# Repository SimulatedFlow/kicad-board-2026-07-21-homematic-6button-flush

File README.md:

# 2026-07-21-homematic-6button-flush

<!-- SF-STORE-BLOCK:BEGIN -->
## 🛒 Source-available — see before you buy

This repository contains the **full design files** of a commercial hardware board. It is **source-available, not open source**: read it, evaluate it, then buy a license to use it. See **LICENSE.md (source-available, purchase required)**.

**Get it / Buy:**
- **Order on eBay** (this board, bare PCB): https://www.ebay.de/itm/398220349166
- Product page (specs, photos, price): https://simulatedflow.teufel-engineering.com/platinen/2026-07-21-homematic-6button-flush/
- eBay store — all our boards and PCB art: https://www.ebay.de/usr/simula-9
- Merch shop (dev & gaming): https://simulatedflow.myspreadshop.de
- Merch shop (Synthetica / EDM): https://synthetica.myspreadshop.de
- Direct / invoice (Simulated Flow UG): simulatedflow@gmail.com

### 📬 **Free Board Documentation & Firmware Pack**

Schematics, BOMs and example-firmware docs for our STM32 carrier boards. Get it by joining the newsletter — plus a heads-up when something new ships. Double opt-in, unsubscribe in one click, no address sharing.

👉 **[Get the free pack](https://simulatedflow.teufel-engineering.com/newsletter/hardware/?q=gh)**

_© 2026 Simulated Flow UG. All rights reserved._
<!-- SF-STORE-BLOCK:END -->

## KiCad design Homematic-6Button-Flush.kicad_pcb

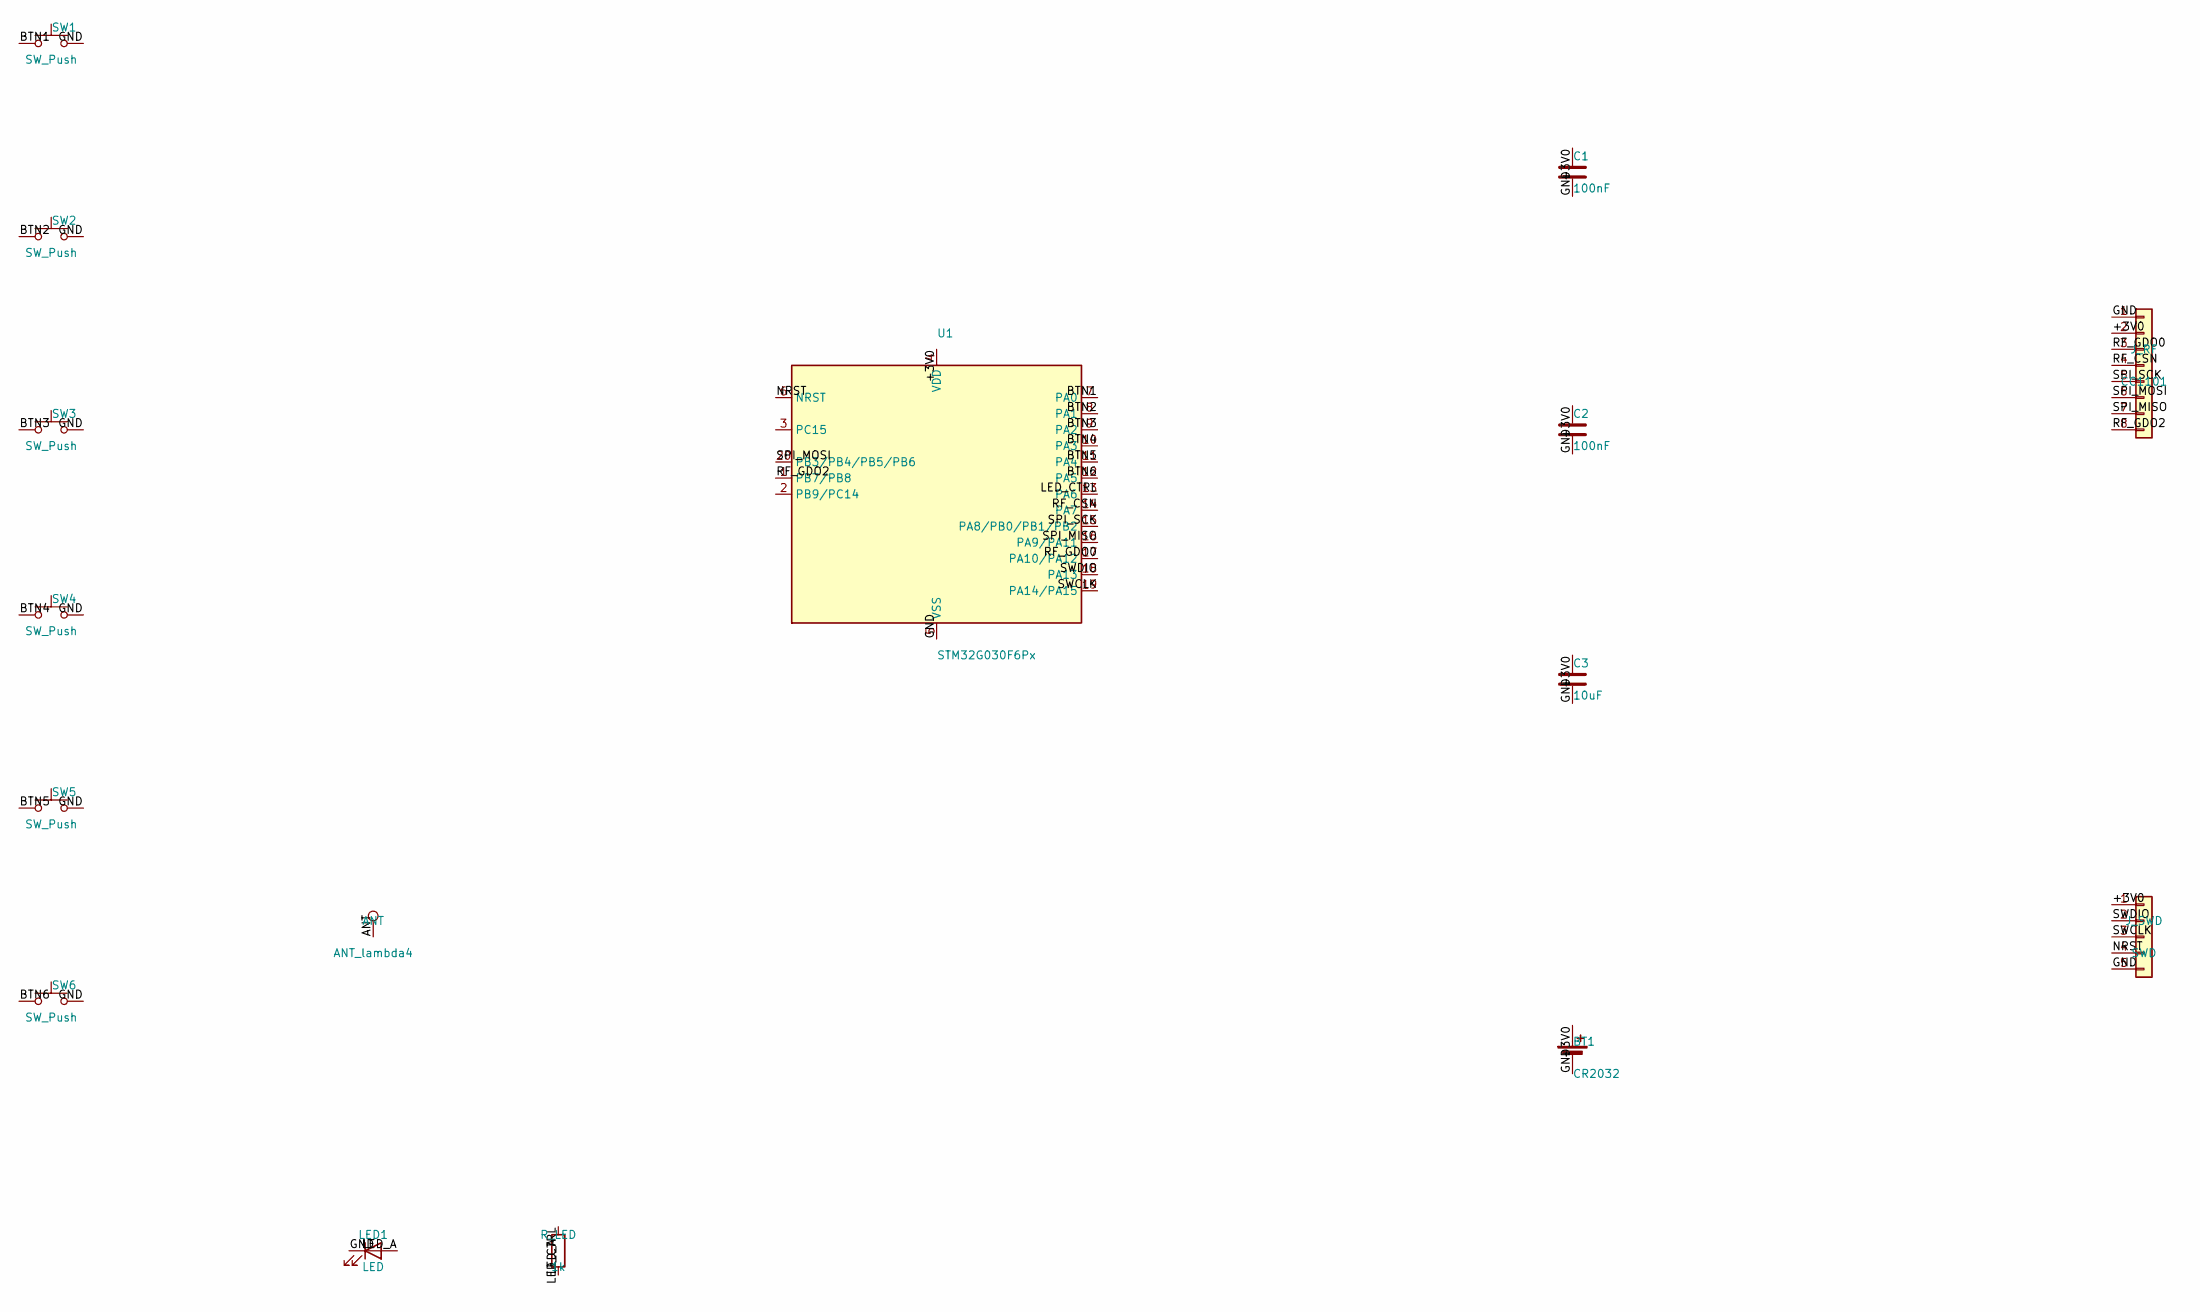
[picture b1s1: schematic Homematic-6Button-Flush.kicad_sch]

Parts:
ANT: ANT_lambda4; TestPoint_Pad_D2.0mm
BT1: CR2032; BatteryHolder_Keystone_3002_1x2032
C1, C2: 100nF; C_0603_1608Metric
C3: 10uF; C_0805_2012Metric
J_RF: CC1101; PinHeader_1x08_P2.54mm_Vertical
J_SWD: SWD; PinHeader_1x05_P2.54mm_Vertical
LED1: LED; LED_0805_2012Metric
R_LED: 1k; R_0603_1608Metric
SW1, SW2, SW3, SW4, SW5, SW6: SW_Push; SW_SPST_B3U-1000P
U1: STM32G030F6Px; TSSOP-20_4.4x6.5mm_P0.65mm

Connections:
+3V0: BT1.1 (+), C1.1, C2.1, C3.1, J_RF.2, J_SWD.1, U1.4 (VDD)
ANT: ANT.1
BTN1: SW1.1, U1.7 (PA0)
BTN2: SW2.1, U1.8 (PA1)
BTN3: SW3.1, U1.9 (PA2)
BTN4: SW4.1, U1.10 (PA3)
BTN5: SW5.1, U1.11 (PA4)
BTN6: SW6.1, U1.12 (PA5)
GND: BT1.2 (-), C1.2, C2.2, C3.2, J_RF.1, J_SWD.5, LED1.1 (K), SW1.2, SW2.2, SW3.2, SW4.2, SW5.2, SW6.2, U1.5 (VSS)
LED_A: LED1.2 (A), R_LED.2
LED_CTRL: R_LED.1, U1.13 (PA6)
NRST: J_SWD.4, U1.6 (NRST)
RF_CSN: J_RF.4, U1.14 (PA7)
RF_GDO0: J_RF.3, U1.17 (PA10/PA12)
RF_GDO2: J_RF.8, U1.1 (PB7/PB8)
SPI_MISO: J_RF.7, U1.16 (PA9/PA11)
SPI_MOSI: J_RF.6, U1.20 (PB3/PB4/PB5/PB6)
SPI_SCK: J_RF.5, U1.15 (PA8/PB0/PB1/PB2)
SWCLK: J_SWD.3, U1.19 (PA14/PA15)
SWDIO: J_SWD.2, U1.18 (PA13)

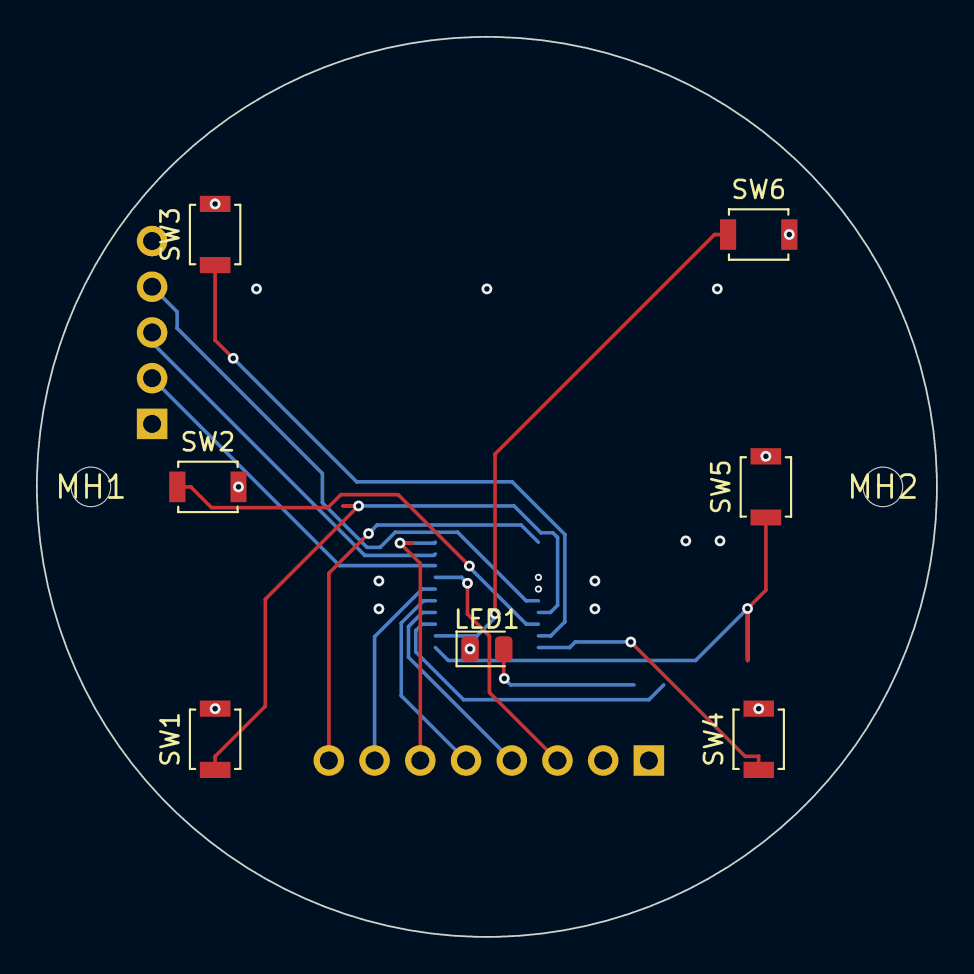
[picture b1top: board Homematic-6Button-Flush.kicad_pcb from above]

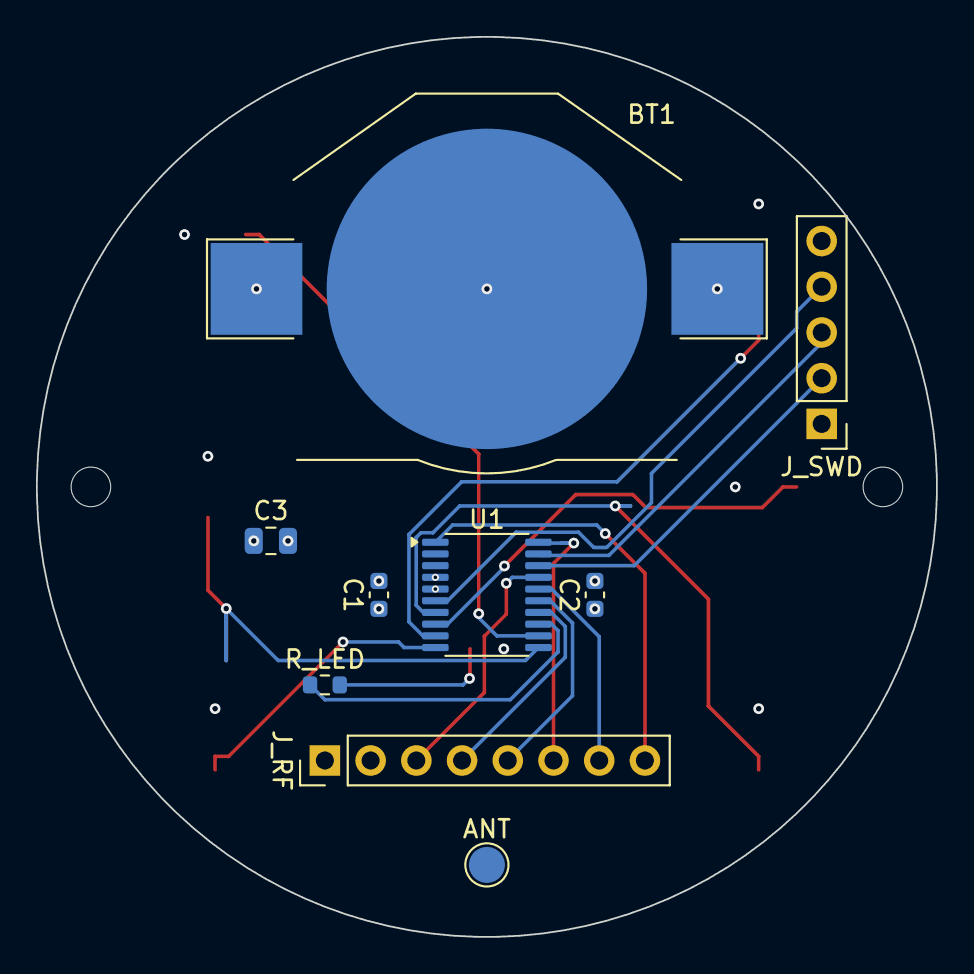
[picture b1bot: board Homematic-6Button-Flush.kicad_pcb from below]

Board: 4 copper layers, 50.0 x 50.0 mm, 18 parts (9 on the bottom side), 19 nets.

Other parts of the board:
MH1, MH2: MountingHole_2.2mm

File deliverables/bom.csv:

"Refs","Value","Footprint","Qty","DNP"
"ANT?","ANT_lambda4","TestPoint:TestPoint_Pad_D2.0mm","1",""
"BT1","CR2032","Battery:BatteryHolder_Keystone_3002_1x2032","1",""
"C1","100nF","Capacitor_SMD:C_0603_1608Metric","1",""
"C2","100nF","Capacitor_SMD:C_0603_1608Metric","1",""
"C3","10uF","Capacitor_SMD:C_0805_2012Metric","1",""
"J_RF?","CC1101","Connector_PinHeader_2.54mm:PinHeader_1x08_P2.54mm_Vertical","1",""
"J_SWD?","SWD","Connector_PinHeader_2.54mm:PinHeader_1x05_P2.54mm_Vertical","1",""
"LED1","LED","LED_SMD:LED_0805_2012Metric","1",""
"R_LED?","1k","Resistor_SMD:R_0603_1608Metric","1",""
"SW1","SW_Push","Button_Switch_SMD:SW_SPST_B3U-1000P","1",""
"SW2","SW_Push","Button_Switch_SMD:SW_SPST_B3U-1000P","1",""
"SW3","SW_Push","Button_Switch_SMD:SW_SPST_B3U-1000P","1",""
"SW4","SW_Push","Button_Switch_SMD:SW_SPST_B3U-1000P","1",""
"SW5","SW_Push","Button_Switch_SMD:SW_SPST_B3U-1000P","1",""
"SW6","SW_Push","Button_Switch_SMD:SW_SPST_B3U-1000P","1",""
"U1","STM32G030F6Px","Package_SO:TSSOP-20_4.4x6.5mm_P0.65mm","1",""
